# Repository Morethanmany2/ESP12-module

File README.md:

# ESP12-module

An esp based Wifi module, designed as the firdt project in KiCAD.

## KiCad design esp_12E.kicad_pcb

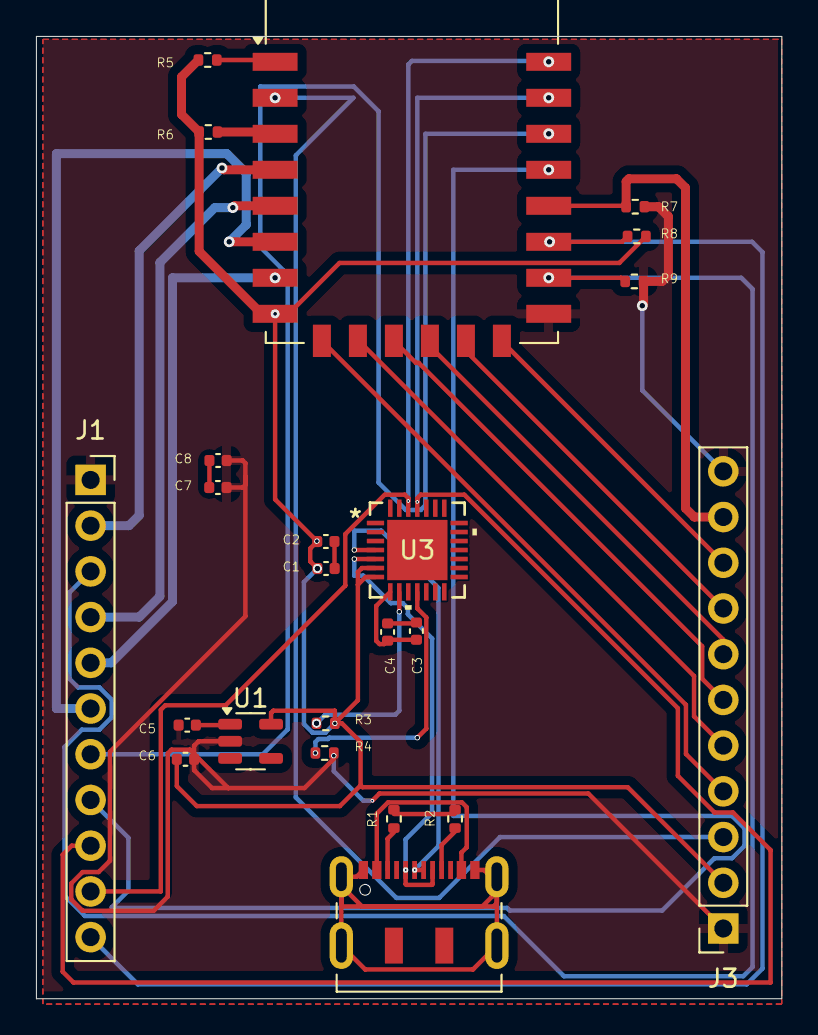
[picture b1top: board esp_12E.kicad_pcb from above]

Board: 2 copper layers, 41.4 x 53.5 mm, 23 parts (0 on the bottom side), 36 nets.

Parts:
C1, C3, C5, C6: 1uF/0402; C_0402_1005Metric
C2, C4: 0.1uF/0402; C_0402_1005Metric
C7: 1uF; C_0402_1005Metric
C8: 0.1 uF; C_0402_1005Metric
J1, J3: Conn_01x11_Socket; PinSocket_1x11_P2.54mm_Vertical
J2: USB_C_Receptacle; USB_C_Receptacle_JAE_DX07S016JA1R1500
R1, R2: 5.1K ohm/0402; R_0402_1005Metric
R3: 4.7K ohm/0402; R_0402_1005Metric
R4: 10K ohm/0402; R_0402_1005Metric
R5, R6, R7, R8, R9: 12K ohm/0402; R_0402_1005Metric
U1: MIC5504-3.3YM5; SOT-23-5
U2: ESP-12E
U3: CP2102-GM; QFN28_5X5_SIL

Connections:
+3V3: C1.1, C2.1, C6.1, J3.2, R3.2, R5.1, R6.1, R8.2, U1.5 (VOUT), U2.8 (VCC), U3.6 (VDD), U3.7 (REGIN)
/ADC: J3.3, U2.2 (ADC)
/CS0: J3.4, U2.9 (CS0)
/Data+: J2.A6 (D+), J2.B6 (D+), U3.4 (D+)
/Data-: J2.A7 (D-), J2.B7 (D-), U3.5 (D-)
/GPIO0: J3.10, R7.1, U2.18 (GPIO0)
/GPIO2: J1.11, R8.1, U2.17 (GPIO2)
/GPIO4: J1.8, U2.19 (GPIO4)
/GPIO5: J1.7, U2.20 (GPIO5)
/GPIO9: J3.6, U2.11 (GPIO9)
/GPIO10: J3.7, U2.12 (GPIO10)
/GPIO12: J1.6, U2.6 (GPIO12)
/GPIO13: J1.5, U2.7 (GPIO13)
/GPIO14: J1.4, U2.5 (GPIO14)
/GPIO15: J1.3, R9.1, U2.16 (GPIO15)
/GPIO16: J1.2, U2.4 (GPIO16)
/MISO: J3.5, U2.10 (MISO)
/MOSI: J3.8, U2.13 (MOSI)
/RXD: J1.9, U2.21 (GPIO3/RXD), U3.25 (RXD)
/SCLK: J3.9, U2.14 (SCLK)
/TXD: J1.10, U2.22 (GPIO1/TXD), U3.26 (TXD)
/nRST: R5.2, U2.1 (~RST)
GND: C5.2, C6.2, C7.2, C8.2, J1.1, J3.1, J3.11, R4.2, R7.2, R9.2, U1.2 (GND), U2.15 (GND), U3.3 (GND)
unnamed: C1.2, C2.2
unnamed: C3.2, C4.2
unnamed: C7.1, C8.1
unnamed: J2.A5 (CC1), R1.1
unnamed: J2.B5 (CC2), R2.1
unnamed: J2.A1 (GND), J2.A12 (GND), J2.B1 (GND), J2.B12 (GND), J2.S1 (SHIELD)
unnamed: J2.A4 (VBUS), J2.A9 (VBUS), J2.B4 (VBUS), J2.B9 (VBUS)
unnamed: R1.2, R2.2
unnamed: C5.1, U1.1 (VIN)
unnamed: R6.2, U2.3 (EN)
unnamed: R3.1, U3.9 (*RST)
unnamed: R4.1, U3.11 (*SUSPEND)
unnamed: C3.1, C4.1, U3.8 (VBUS)

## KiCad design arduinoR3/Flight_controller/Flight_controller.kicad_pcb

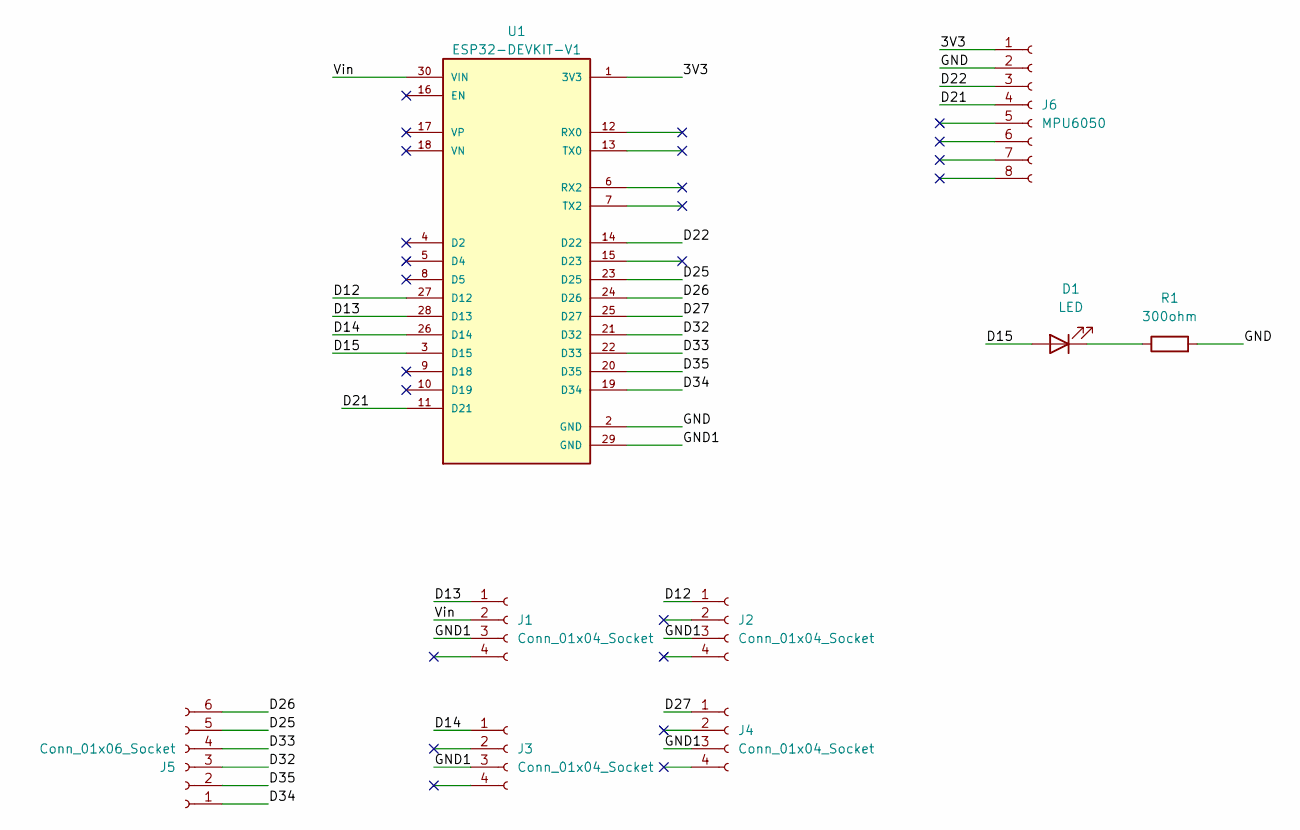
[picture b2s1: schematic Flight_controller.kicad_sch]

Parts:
D1: LED; LED_D3.0mm_FlatTop
J1, J2, J3, J4: Conn_01x04_Socket; PinSocket_1x04_P1.00mm_Vertical
J5: Conn_01x06_Socket; PinSocket_1x06_P1.00mm_Vertical
J6: MPU6050; PinSocket_1x08_P1.00mm_Vertical
R1: 300ohm; R_Axial_DIN0204_L3.6mm_D1.6mm_P1.90mm_Vertical
U1: ESP32-DEVKIT-V1; MODULE_ESP32_DEVKIT_V1; PARTREV N/A

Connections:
/3V3: J6.1 (VCC), U1.1 (3V3)
/D12: J2.1, U1.27 (D12)
/D13: J1.1, U1.28 (D13)
/D14: J3.1, U1.26 (D14)
/D15: D1.2 (A), U1.3 (D15)
/D21: J6.4 (SDA), U1.11 (D21)
/D22: J6.3 (SCL), U1.14 (D22)
/D25: J5.5, U1.23 (D25)
/D26: J5.6, U1.24 (D26)
/D27: J4.1, U1.25 (D27)
/D32: J5.3, U1.21 (D32)
/D33: J5.4, U1.22 (D33)
/D34: J5.1, U1.19 (D34)
/D35: J5.2, U1.20 (D35)
/GND: J6.2 (GND), R1.2, U1.2 (GND)
/GND1: J1.3, J2.3, J3.3, J4.3, U1.29 (GND)
/Vin: J1.2, U1.30 (VIN)
unnamed: D1.1 (K), R1.1

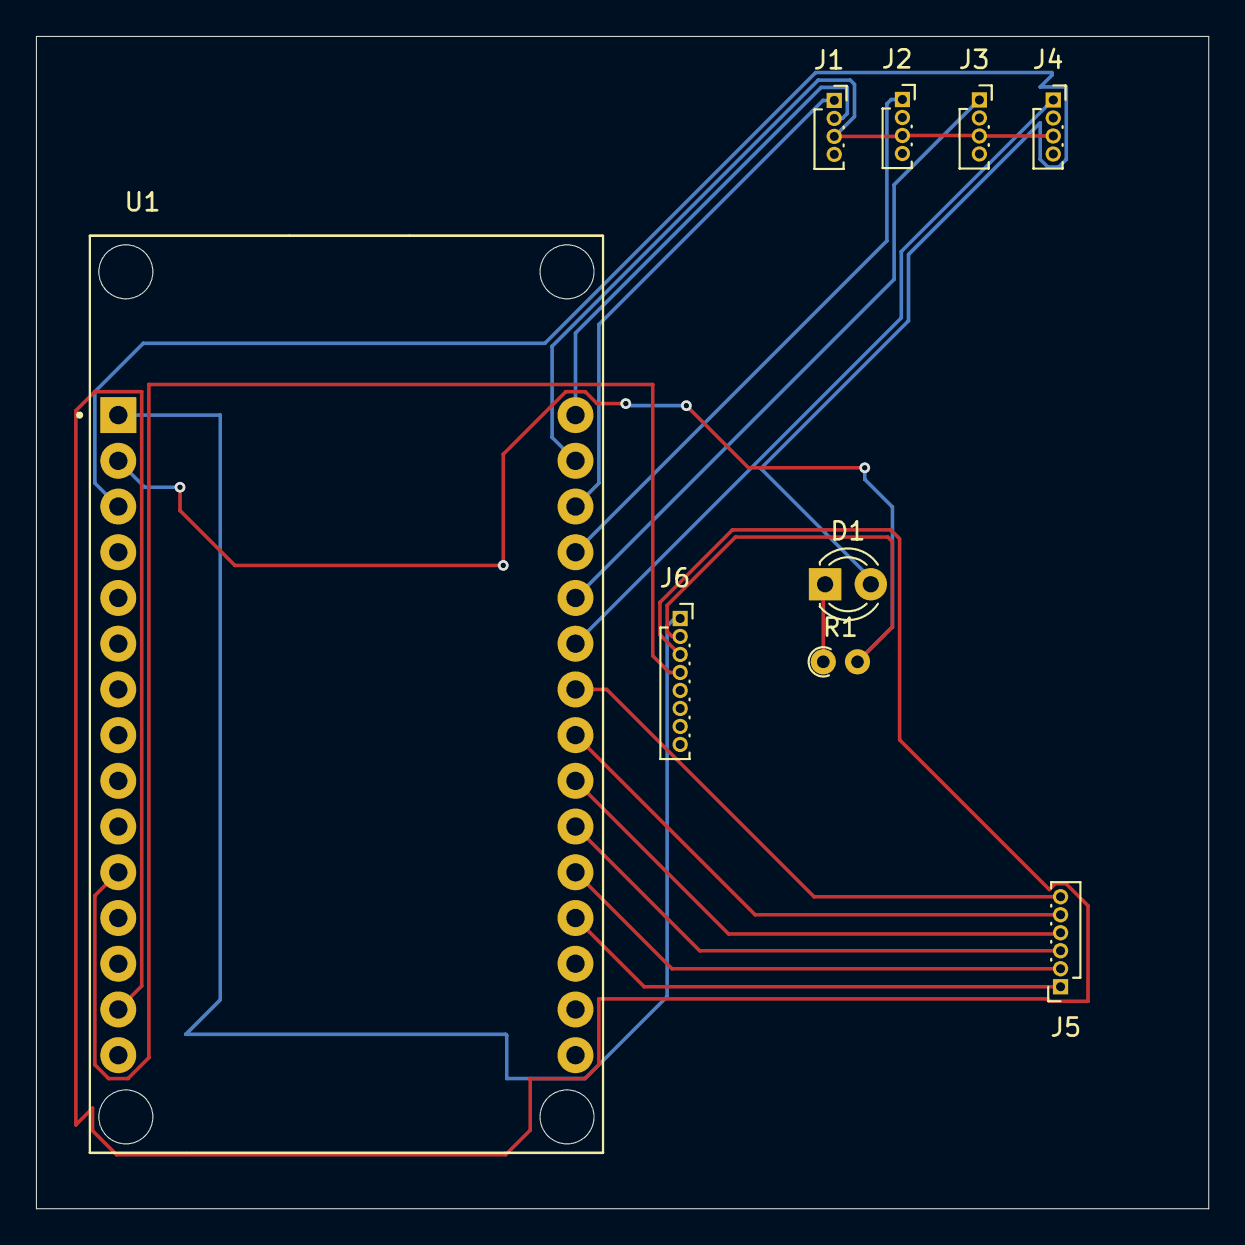
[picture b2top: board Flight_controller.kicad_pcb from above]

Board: 2 copper layers, 65.1 x 65.1 mm, 9 parts (0 on the bottom side), 18 nets.

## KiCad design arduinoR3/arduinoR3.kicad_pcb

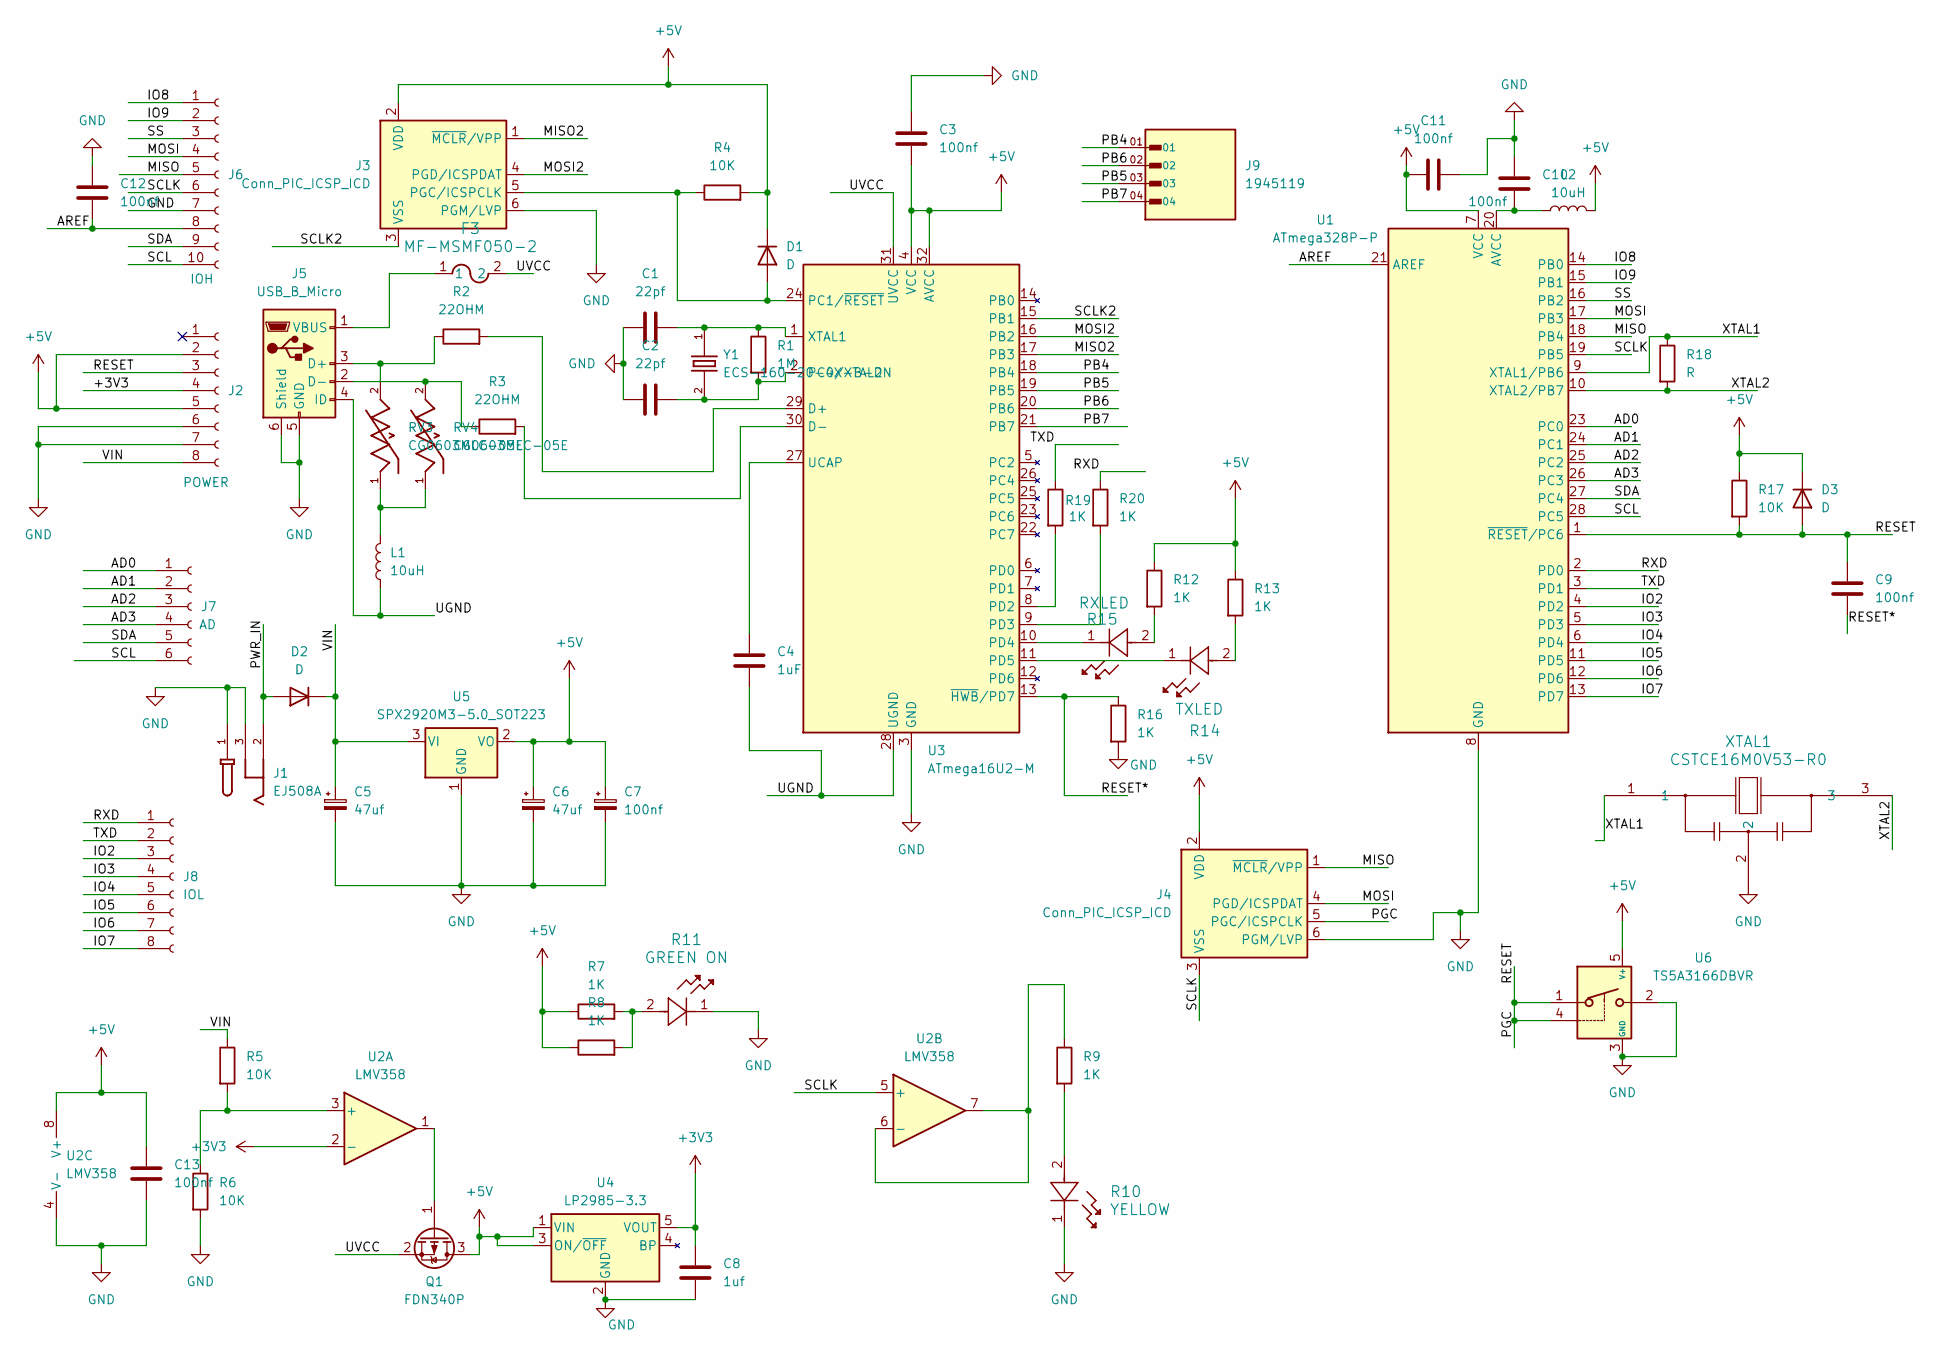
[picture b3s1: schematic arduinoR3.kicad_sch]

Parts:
C1, C2: 22pf; C_0201_0603Metric
C3, C9, C10, C11, C12, C13: 100nf; C_0201_0603Metric
C4: 1uF; C_0201_0603Metric
C5, C6: 47uf; CP_Elec_3x5.3
C7: 100nf; CP_Elec_3x5.3
C8: 1uf; C_0201_0603Metric
D1, D2, D3: D; D_0201_0603Metric
F3: MF-MSMF050-2; Fuse_0603_1608Metric
J1: EJ508A; MPD_EJ508A; PARTREV J
J2: POWER; PinSocket_1x08_P1.00mm_Vertical
J3, J4: Conn_PIC_ICSP_ICD; PinHeader_1x06_P2.54mm_Vertical
J5: USB_B_Micro; USB_Micro-B_GCT_USB3076-30-A
J6: IOH; PinSocket_1x10_P1.00mm_Vertical
J7: AD; PinSocket_1x06_P1.00mm_Vertical
J8: IOL; PinSocket_1x08_P1.00mm_Vertical
J9: 1945119; PHOENIX_1945119; PARTREV 29.05.2019
L1, L2: 10uH; L_0201_0603Metric
Q1: FDN340P; SOT-23
R1: 1M; R_0201_0603Metric
R2, R3: 22OHM; R_0201_0603Metric
R4, R5, R6, R17: 10K; R_0201_0603Metric
R7, R8, R9, R12, R13, R16, R19, R20: 1K; R_0201_0603Metric
R10: YELLOW; LED_SMLD12_ROM
R11: GREEN ON; LED_SMLD12_ROM
R14: TXLED; LED_SMLD12_ROM
R15: RXLED; LED_SMLD12_ROM
R18: R; R_0201_0603Metric
RV3, RV4: CG0603MLC-05E; VARC1608X56N; PARTREV E
U1: ATmega328P-P; DIP-28_W7.62mm
U2: LMV358; LFCSP-8_2x2mm_P0.5mm
U3: ATmega16U2-M; QFN-32-1EP_5x5mm_P0.5mm_EP3.1x3.1mm
U4: LP2985-3.3; SOT-23-5
U5: SPX2920M3-5.0_SOT223; SOT-223-3_TabPin2
U6: TS5A3166DBVR; SOT-23-5
XTAL1: CSTCE16M0V53-R0; Resonator_SMD_Murata_CSTxExxV-3Pin_3.0x1.1mm
Y1: ECS-160-20-4X-B-DN; XTAL_ECS-160-20-4X-B-DN

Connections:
+3V3: C8.1, U2.2 (-), U4.5 (VOUT); also elsewhere on the board
/AD0: J7.1, U1.23 (PC0); also elsewhere on the board
/AD1: J7.2, U1.24 (PC1); also elsewhere on the board
/AD2: J7.3, U1.25 (PC2); also elsewhere on the board
/AD3: J7.4, U1.26 (PC3); also elsewhere on the board
/AREF: C12.2, J6.8, U1.21 (AREF); also elsewhere on the board
/IO2: J8.3, U1.4 (PD2); also elsewhere on the board
/IO3: J8.4, U1.5 (PD3); also elsewhere on the board
/IO4: J8.5, U1.6 (PD4); also elsewhere on the board
/IO5: J8.6, U1.11 (PD5); also elsewhere on the board
/IO6: J8.7, U1.12 (PD6); also elsewhere on the board
/IO7: J8.8, U1.13 (PD7); also elsewhere on the board
/IO8: J6.1, U1.14 (PB0); also elsewhere on the board
/IO9: J6.2, U1.15 (PB1); also elsewhere on the board
/MISO: J4.1 (~MCLR/VPP), J6.5, U1.18 (PB4); also elsewhere on the board
/MISO2: J3.1 (~MCLR/VPP), U3.17 (PB3)
/MOSI: J4.4 (PGD/ICSPDAT), J6.4, U1.17 (PB3); also elsewhere on the board
/MOSI2: J3.4 (PGD/ICSPDAT), U3.16 (PB2)
/PB4: J9.01, U3.18 (PB4)
/PB5: J9.03, U3.19 (PB5)
/PB6: J9.02, U3.20 (PB6)
/PB7: J9.04, U3.21 (PB7)
/PGC: C9.1, D3.2 (A), J2.3, J4.5 (PGC/ICSPCLK), R17.2, U1.1 (~RESET/PC6), U6.1, U6.4; also elsewhere on the board
/PWR_IN: D2.2 (A), J1.2
/RESET*: C9.2, R16.1, U3.13 (~HWB/PD7)
/RXD: J8.1, R20.1, U1.2 (PD0); also elsewhere on the board
/SCL: J6.10, J7.6, U1.28 (PC5); also elsewhere on the board
/SCLK: J4.3 (VSS), J6.6, U1.19 (PB5), U2.5 (+); also elsewhere on the board
/SCLK2: J3.3 (VSS), U3.15 (PB1), U3.e (PB1)
/SDA: J6.9, J7.5, U1.27 (PC4); also elsewhere on the board
/SS: J6.3, U1.16 (PB2); also elsewhere on the board
/TXD: J8.2, R19.1, U1.3 (PD1); also elsewhere on the board
/UGND: C4.2, J5.4 (ID), L1.1, U3.28 (UGND)
/UVCC: F3.2, Q1.2 (S), U3.31 (UVCC)
/VIN: C5.1, D2.1 (K), J2.8, R5.1, U5.3 (VI); also elsewhere on the board
/XTAL1: R18.1, U1.9 (XTAL1/PB6), XTAL1.1
/XTAL2: R18.2, U1.10 (XTAL2/PB7), XTAL1.3
unnamed: D1.2 (A), J3.5 (PGC/ICSPCLK), R4.1, U3.24 (PC1/~RESET)
unnamed: J5.3 (D+), R2.1, RV3.2
unnamed: J5.2 (D-), R3.1, RV4.2
unnamed: F3.1, J5.1 (VBUS)
unnamed: L1.2, RV3.1, RV4.1
unnamed: Q1.1 (G), U2.1
unnamed: R9.2, R10.2
unnamed: R7.2, R8.2, R11.2
unnamed: R12.2, R15.2
unnamed: R13.2, R14.2
unnamed: C10.2, L2.1, U1.20 (AVCC)
unnamed: R5.2, R6.1, U2.3 (+)
unnamed: R9.1, U2.6 (-), U2.7
unnamed: R2.2, U3.29 (D+)
unnamed: R3.2, U3.30 (D-)
unnamed: C2.2, R1.2, U3.2 (PC0/XTAL2), Y1.2
unnamed: R19.2, U3.8 (PD2)
unnamed: R20.2, U3.9 (PD3)
unnamed: R15.1, U3.10 (PD4)
unnamed: R14.1, U3.11 (PD5)
unnamed: C4.1, U3.27 (UCAP)
unnamed: C1.2, R1.1, U3.1 (XTAL1), Y1.1

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
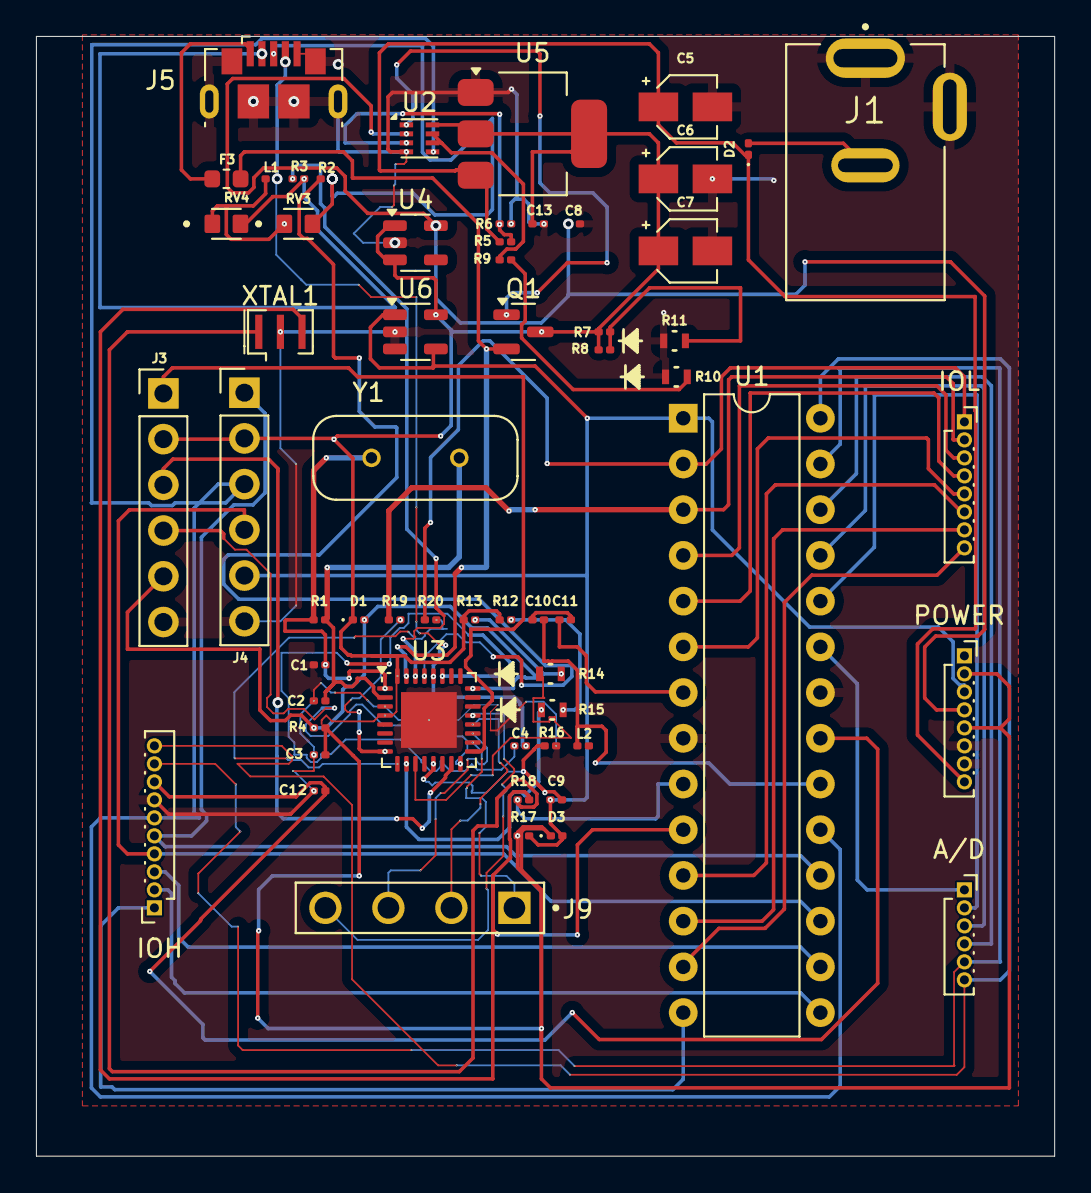
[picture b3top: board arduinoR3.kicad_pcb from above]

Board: 2 copper layers, 56.6 x 62.2 mm, 59 parts (0 on the bottom side), 63 nets.

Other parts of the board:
A/D: AD; PinSocket_1x06_P1.00mm_Vertical
IOH: IOH; PinSocket_1x10_P1.00mm_Vertical
IOL: IOL; PinSocket_1x08_P1.00mm_Vertical
POWER: POWER; PinSocket_1x08_P1.00mm_Vertical

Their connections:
+3V3: POWER.4; also elsewhere on the board
/AD0: A/D.1; also elsewhere on the board
/AD1: A/D.2; also elsewhere on the board
/AD2: A/D.3; also elsewhere on the board
/AD3: A/D.4; also elsewhere on the board
/AREF: IOH.8; also elsewhere on the board
/IO2: IOL.3; also elsewhere on the board
/IO3: IOL.4; also elsewhere on the board
/IO4: IOL.5; also elsewhere on the board
/IO5: IOL.6; also elsewhere on the board
/IO6: IOL.7; also elsewhere on the board
/IO7: IOL.8; also elsewhere on the board
/IO8: IOH.1; also elsewhere on the board
/IO9: IOH.2; also elsewhere on the board
/MISO: IOH.5; also elsewhere on the board
/MOSI: IOH.4; also elsewhere on the board
/PGC: POWER.3; also elsewhere on the board
/RXD: IOL.1; also elsewhere on the board
/SCL: A/D.6, IOH.10; also elsewhere on the board
/SCLK: IOH.6; also elsewhere on the board
/SDA: A/D.5, IOH.9; also elsewhere on the board
/SS: IOH.3; also elsewhere on the board
/TXD: IOL.2; also elsewhere on the board
/VIN: POWER.8; also elsewhere on the board
